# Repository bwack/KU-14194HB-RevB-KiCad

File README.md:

# KU-14194HB-RevB-KiCad

The rare KU14194HB C64 Motherboard schematics and layout. Retraced in and imported from SprintLayout.

[Disclaimer](https://github.com/bwack/KU-14194HB-RevB-KiCad/blob/master/DISCLAIMER.md)

# Original bodges

This PCB is a replica. It includes the mistakes that Commodore made.

It is necessary to cut a trace above R37 on the bottom side, and add a 1K resistor from R37 and up to a via.
See the images folder to where to cut and add a resistor.

Piggyback a 100nF capacitor over CR1.

Notice how the main crystal oscillator Y1 body is grounded with a wire.

In later designs 250407 Reb B I think, 4 piggybacked diodes were introduced to protect the serial lines when hotplugging the disc drive.
I haven't added these myself, but I see the value of having those. I might add instructions here later on how to add the diodes.

# BOM

Please see the [BOM file](bom.csv).

# Interactive-BOM

[The interactive bom html page](https://htmlpreview.github.io/?https://raw.githubusercontent.com/bwack/KU-14194HB-RevB-KiCad/master/interactive-bom/ibom.html) is useful for assembling the board and finding signal traces by using a web browser. Try it here. For a BOM for ordering parts see the BOM above.

# Questions

* Feel free post questions in the issues section. I will provide more information here later.

# Change log

- 2020-01-23: V1.4 PCB improvements:
  - Expansion Port: Larger round solder pads for the shield. Same error in the original.
  - Expansion Port: Connector moved to center of shield. Some traces moved.
  - Left edge: Extended the PCB by 2.2mm.
  - Left edge: Increased track width of the power rails.
  - CAN shield: added two solder pads.
  - RF modulator: added solder pad.
  - Schematics: Rev 1.4. No change.
- 2019-11-12: V1.3 Fixes: Mostly missing values.
  - C88: "1000uF 25V" -> "470uF 50uF". Commodore said 1000 but used 470.
  - R31: "180" -> "1K". A mistake in the commodore schematics.
  - R52: "?" -> "330"
  - R53: "?" -> "100"
  - C86: "?" -> "82pF",
  - C36: "0.1" -> "20pF",
  - R22: missing trace. R22 = 0 Ohm. Parallel to C87 (NC). R22 doesn't matter.
  - C101: is a Y5U. VIC2's decoupling cap. Has a higher dielectric rating. Doesn't matter.
  - C70: 15pF 5%. This is a PAL only board. In later revisions, 16pF is used for NTSC.
 - 2019-11-10 V1.2 Added missing C14 10uF 25V electrolytic capacitor
- 2019-10-15 V1.1 Layout: Fixed missing keying-slot in user port.
- 2019-10-05 V1.0 First release.

# YouTube

A playlist of all the videos:

[](
https://www.youtube.com/watch?v=iNxOm7G6efA&list=PLtQOf_JULmrTGLZCElGG_T1a01JSDP0CP)

# In the wind

forum64.de: The board has some threads at forum64.de (German). May require login.
* [Bilder SHOWROOM für Repro-Boards... KU-14194HB](https://www.forum64.de/index.php?thread/97205-bilder-showroom-f%C3%BCr-repro-boards-ku-14194hb/&pageNo=1)
* [KU-14194 Bestückungs-Thread](https://www.forum64.de/index.php?thread/96336-ku-14194-best%C3%BCckungs-thread/)
* [KU-14194](https://www.forum64.de/index.php?thread/95454-ku-14194/) (long group buy thread)
* [KU-14194 (Replika) ... wer schafft es als Erste/r? Aktuelle Sachstandsberichte ...](https://www.forum64.de/index.php?thread/95518-ku-14194-replika-wer-schafft-es-als-erste-r-aktuelle-sachstandsberichte/)

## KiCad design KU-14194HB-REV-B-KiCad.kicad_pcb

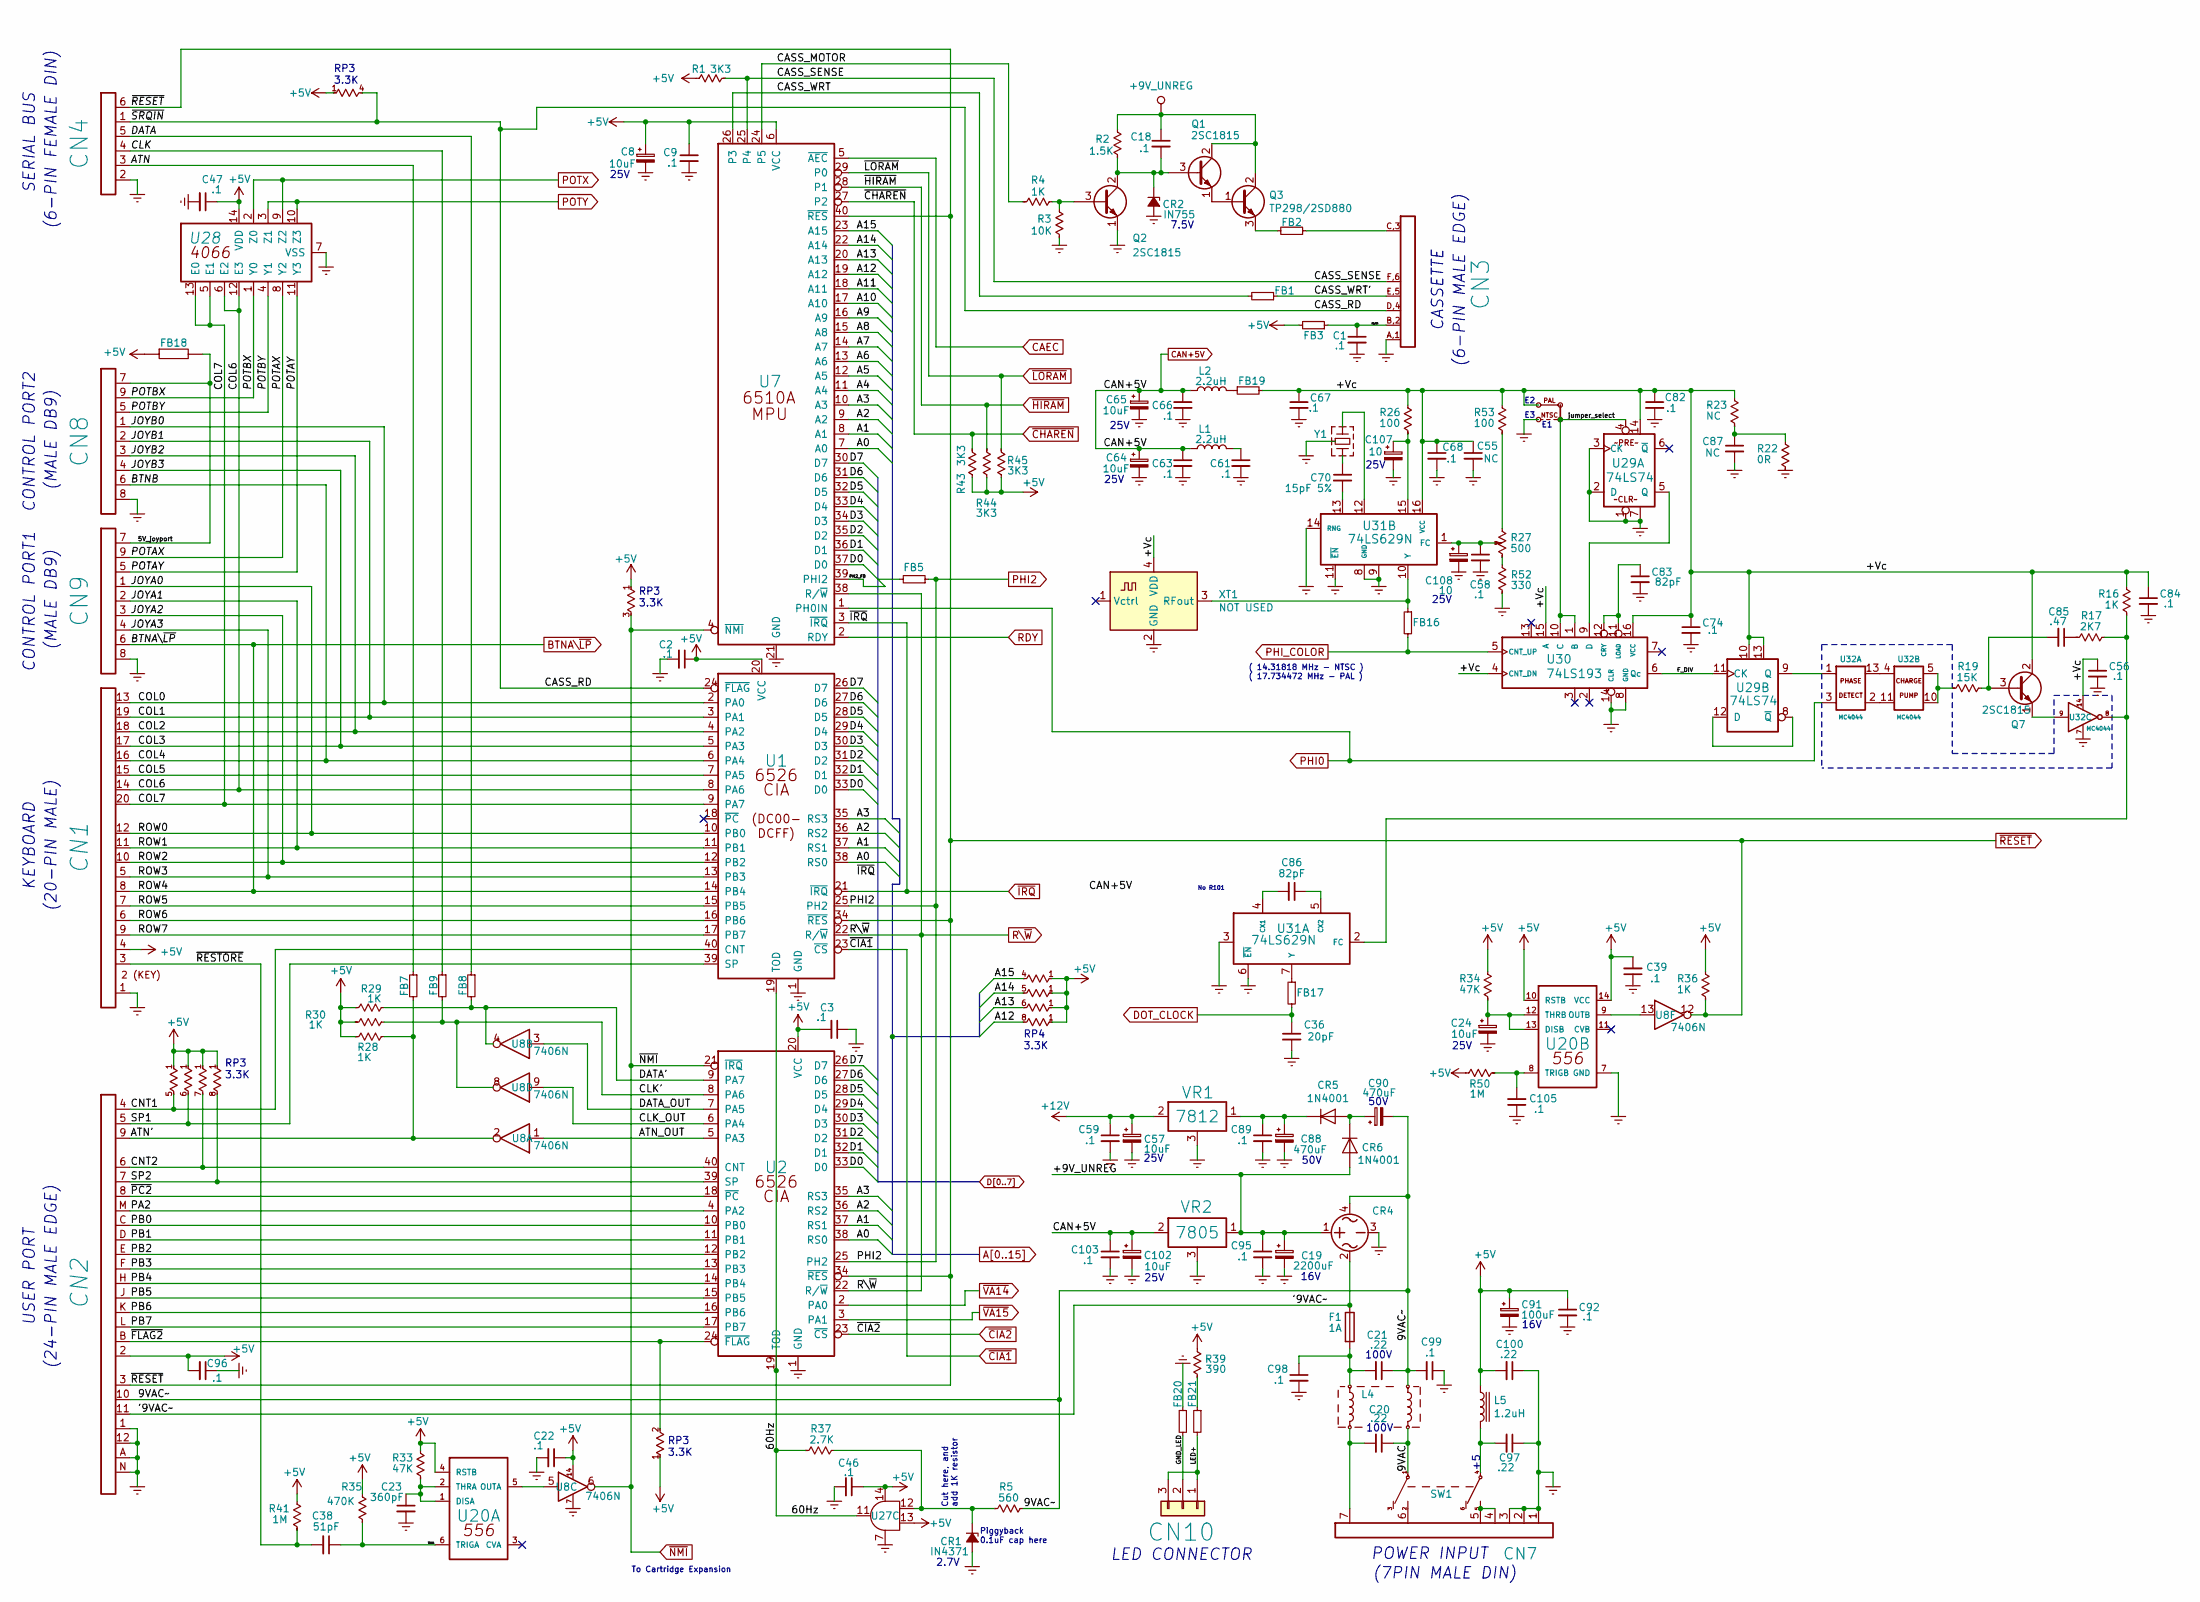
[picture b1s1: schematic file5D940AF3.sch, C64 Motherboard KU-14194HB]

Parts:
C1, C2, C3, C9, C18, C22, C39, C46, C47, C56, C58, C59, C61, C63, C66, C67, C68, C74, C82, C84, C89, C92, C95, C96, C98, C99, C103, C105: .1; CAP_P5.08mm
C8, C24, C57, C64, C65, C102: 10uF; CAP_ELYT_RADIAL_P2.54mm
C19: 2200uF; LARGE_ELECTROLYTIC_33x18_P38.10mm_AXIAL_TH
C20, C21: .22; CAP_POLY_100V_TH_P10.16mm
C23: 360pF; CAP_AXIAL_P12.7mm
C36: 20pF; RESISTOR
C38: 51pF; CAP_AXIAL_P12.7mm
C55, C87: NC; CAP_P5.08mm
C70: 15pF 5%; RESISTOR
C83, C86: 82pF; RESISTOR
C85: .47; CAP_P5.08mm
C88, C90: 470uF; LARGE_ELECTROLYTIC_33x18_P38.10mm_AXIAL_TH
C91: 100uF; CAP_ELYT_RADIAL_P5.08mm
C97, C100: .22; CAP_P5.08mm
C107, C108: 10; CAP_ELYT_RADIAL_P2.54mm
CN1: KEYBOARD_20PIN_MALE; KEYBOARD_CON
CN2: USER_PORT_CON; EDGE_CON_24P
CN3: CASSETTE_PORT_CON; EDGE_CON_12P_TAPE
CN4: SERIAL_BUS_CON; SERIAL_CON_DIN6
CN7: POWER_CON; POWER_CON_DIN7
CN8, CN9: CONTROL_PORT; JOYPORT_DB9
CN10: LED_CONNECTOR; LED_CON
CR1: IN4371; ZENER_12.7mm
CR2: IN755; ZENER_12.7mm
CR4: BRIDGE_RECTIFIER
CR5, CR6: 1N4001; RECTIFIER_TH_P12.7mm
E1: JUMPER_WIRE
F1: 1A; FUSE
FB1, FB2, FB3, FB5, FB7, FB8, FB9, FB16, FB17, FB19, FB20, FB21: FERRITE_NARROW; FERRITE_BEAD_TH_P12.7mm
FB18: FERRITE_BEAD; FERRITE_BEAD_TH_P12.7mm
L1, L2: 2.2uH; RESISTOR
L4: CHOKE
L5: 1.2uH; INDUCTOR_P15.24mm
Q1, Q2, Q7: 2SC1815; Q_NPN_ECB
Q3: TP298/2SD880; TO-220-3_Vertical
R1, R43, R44, R45: 3K3; RESISTOR
R2: 1.5K; RESISTOR
R3: 10K; RESISTOR
R4, R16, R28, R29, R30, R36: 1K; RESISTOR
R5: 560; RESISTOR
R17: 2K7; RESISTOR
R19: 15K; RESISTOR
R22: 0R; RESISTOR
R23: NC; RESISTOR
R26, R53: 100; RESISTOR
R27: 500; POTMETER
R33, R34: 47K; RESISTOR
R35: 470K; RESISTOR
R37: 2.7K; RESISTOR
R39: 390; RESISTOR
R41, R50: 1M; RESISTOR
R52: 330; RESISTOR
RP3: R_ARRAY_7WAY_US; RP_ARRAY_7WAY
RP4: R_ARRAY_9WAY_US; RP_ARRAY_9WAY
SW1: POWER_SWITCH
U1: CIA_U1; DIP40
U2: CIA_U2; DIP40
U7: 6510_MPU; DIP40
U8: 7406N; DIP14
U20: 556; DIP14
U27: 7408_U27; DIP14
U28: 4066_U28; DIP14
U29: 74LS74; DIP14
U30: 74LS193; DIP16
U31: 74LS629N; DIP16
U32: MC4044; DIP14
VR1: 7812; VOTLAGE_REGULATOR_TO220
VR2: 7805; VOTLAGE_REGULATOR_TO220
XT1: NOT USED; DIP4_DIP14_but_4_pins
Y1: Crystal; CRYSTAL

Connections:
+5V: C2.1, C3.2, C8.1, C9.1, C22.1, C39.2, C46.1, C47.1, C91.1, C92.1, C96.2, C100.2, CN1.4, CN2.2, FB3.2, FB18.1, L5.1, R1.1, R28.2, R29.2, R30.2, R33.1, R34.1, R35.1, R36.1, R39.1, R41.1, R43.1, R44.1, R45.1, R50.1, RP3.1, RP4.1, U1.20 (VCC), U2.20 (VCC), U7.6 (VCC), U8.14, U20.4 (RSTB), U20.10 (RSTB), U20.14 (VCC), U27.13, U27.14, U28.14 (VDD); also elsewhere on the board
+9V_UNREG: C18.1, C19.1, C95.1, CR4.1, CR6.2 (A), Q1.2 (C), Q3.2 (C), R2.1, VR2.1; also elsewhere on the board
+12V: C57.1, C59.1, VR1.2; also elsewhere on the board
/Sheet1/5V_FB3: C1.1, CN3.B,2, FB3.1
/Sheet1/5V_joyport: CN8.7, CN9.7, FB18.2
/Sheet1/9VAC: C20.1, L4.3, SW1.1
/Sheet1/9VAC~~: C21.1, C90.2, C99.2, CN2.10, CR4.4, L4.4, R5.1
/Sheet1/60Hz: R37.2, U1.19 (TOD), U2.19 (TOD), U27.11
/Sheet1/'9VAC~~: CN2.11, CR4.2, F1.1
/Sheet1/+Vc: C55.1, C56.1, C67.1, C68.1, C74.1, C82.1, C84.1, E1.1, FB19.2, Q7.2 (C), R16.1, R23.1, R26.1, R53.1, U29.10, U29.13, U29.14, U30.4 (CNT_DN), U30.15 (A), U30.16 (VCC), U31.16 (VCC), U32.14, XT1.4 (VDD)
/Sheet1/ATN: CN4.3, FB7.1
/Sheet1/ATN': CN2.9, FB7.2, R28.1, U8.2
/Sheet1/ATN_OUT: U2.5 (PA3), U8.1
/Sheet1/BTNB: CN1.16, CN8.6, U1.6 (PA4)
/Sheet1/CASS_MOTOR: R4.2, U7.24 (P5)
/Sheet1/CASS_RD: CN3.D,4, CN4.1, RP3.4, U1.24 (~FLAG~)
/Sheet1/CASS_SENSE: CN3.F,6, R1.2, U7.25 (P4)
/Sheet1/CASS_WRT: FB1.2, U7.26 (P3)
/Sheet1/CASS_WRT': CN3.E,5, FB1.1
/Sheet1/CLK: CN4.4, FB9.1
/Sheet1/CLK': FB9.2, R30.1, U2.8 (PA6), U8.8
/Sheet1/CLK_OUT: U2.6 (PA4), U8.9
/Sheet1/CNT1: CN2.4, RP3.5, U1.40 (CNT)
/Sheet1/CNT2: CN2.6, RP3.7, U2.40 (CNT)
/Sheet1/COL0: CN1.13, CN8.1, U1.2 (PA0)
/Sheet1/COL1: CN1.19, CN8.2, U1.3 (PA1)
/Sheet1/COL2: CN1.18, CN8.3, U1.4 (PA2)
/Sheet1/COL3: CN1.17, CN8.4, U1.5 (PA3)
/Sheet1/COL5: CN1.15, U1.7 (PA5)
/Sheet1/COL6: CN1.14, U1.8 (PA6), U28.6 (E2), U28.12 (E3)
/Sheet1/COL7: CN1.20, U1.9 (PA7), U28.5 (E1), U28.13 (E0)
/Sheet1/DATA: CN4.5, FB8.1
/Sheet1/DATA': FB8.2, R29.1, U2.9 (PA7), U8.4
/Sheet1/DATA_OUT: U2.7 (PA5), U8.3
/Sheet1/F_DIV: U29.11 (CK), U30.6 (Qc)
/Sheet1/GND_LED: CN10.2, FB20.2
/Sheet1/JOYA0: CN1.12, CN9.1, U1.10 (PB0)
/Sheet1/JOYA1: CN1.11, CN9.2, U1.11 (PB1)
/Sheet1/JOYA2: CN1.10, CN9.3, U1.12 (PB2)
/Sheet1/JOYA3: CN1.5, CN9.4, U1.13 (PB3)
/Sheet1/LED+: CN10.1, CN10.3, FB21.2
/Sheet1/PA2: CN2.M, U2.4 (PA2)
/Sheet1/PB0: CN2.C, U2.10 (PB0)
/Sheet1/PB1: CN2.D, U2.11 (PB1)
/Sheet1/PB2: CN2.E, U2.12 (PB2)
/Sheet1/PB3: CN2.F, U2.13 (PB3)
/Sheet1/PB4: CN2.H, U2.14 (PB4)
/Sheet1/PB5: CN2.J, U2.15 (PB5)
/Sheet1/PB6: CN2.K, U2.16 (PB6)
/Sheet1/PB7: CN2.L, U2.17 (PB7)
/Sheet1/PH2_FB: FB5.2, U7.39 (PHI2)
/Sheet1/POTAX: CN9.9, U28.8 (Y2)
/Sheet1/POTAY: CN9.5, U28.11 (Y3)
/Sheet1/POTBX: CN8.9, U28.1 (Y0)
/Sheet1/POTBY: CN8.5, U28.4 (Y1)
/Sheet1/ROW5: CN1.7, U1.15 (PB5)
/Sheet1/ROW6: CN1.6, U1.16 (PB6)
/Sheet1/ROW7: CN1.9, U1.17 (PB7)
/Sheet1/SP1: CN2.5, RP3.6, U1.39 (SP)
/Sheet1/SP2: CN2.7, RP3.8, U2.39 (SP)
/Sheet1/TRIGA: C38.1, R35.2, U20.6 (TRIGA)
/Sheet1/jumper_select: E1.C, U29.4, U30.1 (B), U30.10 (C)
/Sheet1/~FLAG2~: CN2.B, RP3.2, U2.24 (~FLAG~)
/Sheet1/~PC2~: CN2.8, U2.18 (~PC~)
/Sheet1/~RESTORE~: C38.2, CN1.3, R41.2
A0: U1.38 (RS0), U2.38 (RS0), U7.7 (A0); also elsewhere on the board
A1: U1.37 (RS1), U2.37 (RS1), U7.8 (A1); also elsewhere on the board
A2: U1.36 (RS2), U2.36 (RS2), U7.9 (A2); also elsewhere on the board
A3: U1.35 (RS3), U2.35 (RS3), U7.10 (A3); also elsewhere on the board
A4: U7.11 (A4); also elsewhere on the board
A5: U7.12 (A5); also elsewhere on the board
A6: U7.13 (A6); also elsewhere on the board
A7: U7.14 (A7); also elsewhere on the board
A8: U7.15 (A8); also elsewhere on the board
A9: U7.16 (A9); also elsewhere on the board
A10: U7.17 (A10); also elsewhere on the board
A11: U7.18 (A11); also elsewhere on the board
A12: RP4.8, U7.19 (A12); also elsewhere on the board
A13: RP4.6, U7.20 (A13); also elsewhere on the board
A14: RP4.5, U7.22 (A14); also elsewhere on the board
A15: RP4.4, U7.23 (A15); also elsewhere on the board
BTNA\~LP~: CN1.8, CN9.6, U1.14 (PB4); also elsewhere on the board
CAEC: U7.5 (~AEC~); also elsewhere on the board
CAN+5V: C63.1, C64.1, C65.1, C66.1, C102.1, C103.1, L1.1, L2.1, VR2.2; also elsewhere on the board
D0: U1.33 (D0), U2.33 (D0), U7.37 (D0); also elsewhere on the board
D1: U1.32 (D1), U2.32 (D1), U7.36 (D1); also elsewhere on the board
D2: U1.31 (D2), U2.31 (D2), U7.35 (D2); also elsewhere on the board
D3: U1.30 (D3), U2.30 (D3), U7.34 (D3); also elsewhere on the board
D4: U1.29 (D4), U2.29 (D4), U7.33 (D4); also elsewhere on the board
D5: U1.28 (D5), U2.28 (D5), U7.32 (D5); also elsewhere on the board
D6: U1.27 (D6), U2.27 (D6), U7.31 (D6); also elsewhere on the board
D7: U1.26 (D7), U2.26 (D7), U7.30 (D7); also elsewhere on the board
DOT_CLOCK: C36.1, FB17.2; also elsewhere on the board
unnamed: C18.2, CR2.1 (K), Q1.3 (B), Q2.2 (C), R2.2
unnamed: C20.2, CN7.7, L4.2
unnamed: C21.2, C98.1, F1.2, L4.1
unnamed: C23.1, R33.2, U20.1 (DISA), U20.2 (THRA)
unnamed: C24.1, R34.2, U20.12 (THRB), U20.13 (DISB)
unnamed: C61.1, L1.2
unnamed: C70.1, Y1.2
unnamed: C70.2, U31.13
unnamed: C83.1, U30.11 (LOAD), U30.12 (CRY)
unnamed: C85.1, R17.2
unnamed: C85.2, Q7.3 (B), R19.1
unnamed: C86.1, U31.5 (CX2)
unnamed: C86.2, U31.4 (CX1)
unnamed: C87.1, R22.1, R23.2
unnamed: C88.1, C89.1, CR5.1 (K), VR1.1
unnamed: C90.1, CR5.2 (A), CR6.1 (K)
unnamed: C97.2, L5.2, SW1.4
unnamed: C105.2, R50.2, U20.8 (TRIGB)
unnamed: C107.1, R26.2, U31.15
unnamed: C58.1, C108.1, R27.3, U31.1 (FC)
unnamed: CN3.C,3, FB2.1
unnamed: CN7.4, CN7.5, SW1.5
unnamed: CN7.6, SW1.2
unnamed: CR1.1 (K), R5.2, R37.1, U27.12
unnamed: FB2.2, Q3.3 (E)
unnamed: FB16.1, U31.10 (Y), XT1.3 (RFout)
unnamed: FB17.1, U31.7 (Y)
unnamed: FB19.1, L2.2
unnamed: FB21.1, R39.2
unnamed: Q1.1 (E), Q3.1 (B)
unnamed: Q2.3 (B), R3.1, R4.1
unnamed: Q7.1 (E), U32.9
unnamed: R16.2, R17.1, U31.2 (FC), U32.8
unnamed: R19.2, U32.5, U32.10
unnamed: R27.1, R53.2
unnamed: R27.2, R52.1
unnamed: U8.5, U20.5 (OUTA)
unnamed: U8.13, U20.9 (OUTB)
unnamed: U29.5 (Q), U30.9 (D)
unnamed: U29.9 (Q), U32.1
unnamed: U29.8 (~Q~), U29.12 (D)
unnamed: U31.12, Y1.1
unnamed: U32.2, U32.11
unnamed: U32.4, U32.13
PHI0: U7.1 (PH0IN), U32.3; also elsewhere on the board
PHI2: FB5.1, U1.25 (PH2), U2.25 (PH2); also elsewhere on the board
PHI_COLOR: FB16.2, U30.5 (CNT_UP); also elsewhere on the board
POTX: U28.2 (Z0), U28.9 (Z2); also elsewhere on the board
POTY: U28.3 (Z1), U28.10 (Z3); also elsewhere on the board
RDY: U7.2 (RDY); also elsewhere on the board
R\~W~: U1.22 (R/~W~), U2.22 (R/~W~), U7.38 (R/~W~); also elsewhere on the board
~CHAREN~: R43.2, U7.27 (P2); also elsewhere on the board
~CIA1~: U1.23 (~CS~); also elsewhere on the board
~CIA2~: U2.23 (~CS~); also elsewhere on the board
~HIRAM~: R44.2, U7.28 (P1); also elsewhere on the board
~IRQ~: U1.21 (~IRQ~), U7.3 (~IRQ~); also elsewhere on the board
~LORAM~: R45.2, U7.29 (P0); also elsewhere on the board
~NMI~: RP3.3, U2.21 (~IRQ~), U7.4 (~NMI~), U8.6; also elsewhere on the board
~RESET~: CN2.3, CN4.6, R36.2, U1.34 (~RES~), U2.34 (~RES~), U7.40 (~RES~), U8.12; also elsewhere on the board
~VA14~: U2.2 (PA0); also elsewhere on the board
~VA15~: U2.3 (PA1); also elsewhere on the board

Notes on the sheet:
SERIAL BUS
(6-PIN FEMALE DIN)
(24-PIN MALE EDGE)
USER PORT
RP3 3.3K
KEYBOARD
(20-PIN MALE)
(MALE DB9)
CONTROL PORT2
CONTROL PORT1
25V
2.7V
Cut here, and add 1K resistor
Piggyback 0.1uF cap here
RP4 3.3K
7.5V
(6-PIN MALE EDGE)
CASSETTE
LED CONNECTOR
100V
POWER INPUT
(7PIN MALE DIN)
16V
50V
No R101
( 14.31818 MHz - NTSC ) ( 17.734472 MHz - PAL )
To Cartridge Expansion

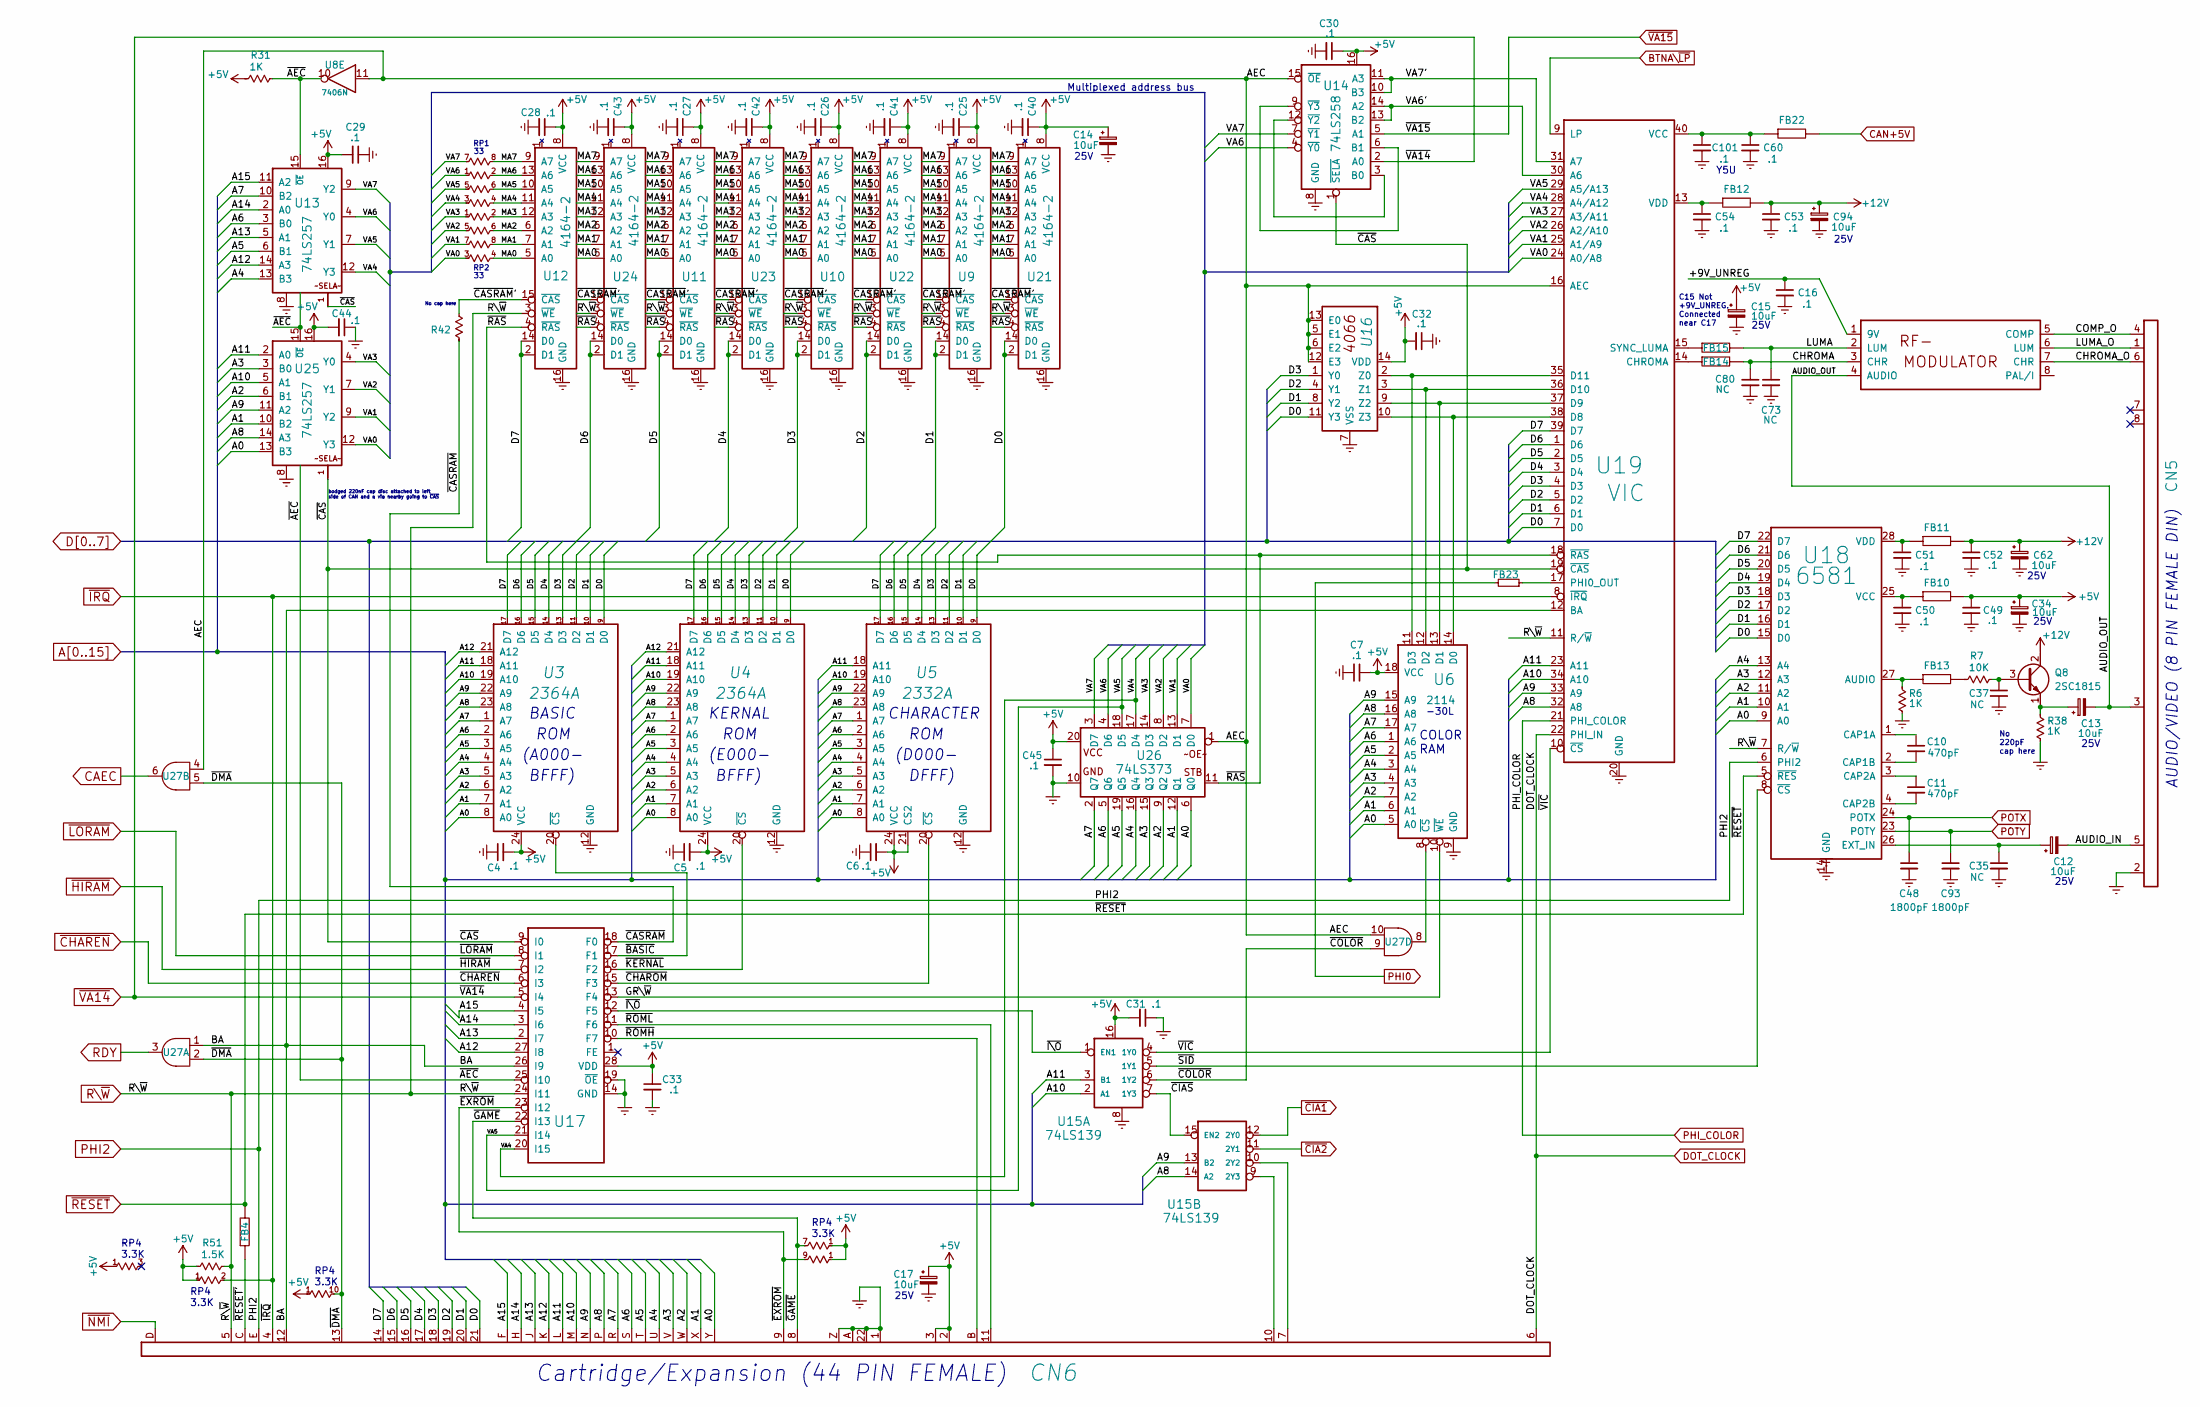
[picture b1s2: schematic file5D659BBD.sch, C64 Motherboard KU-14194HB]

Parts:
C4, C5, C6, C7, C16, C25, C26, C27, C28, C29, C30, C31, C32, C33, C40, C41, C42, C43, C44, C45, C50, C51, C53, C54, C60, C101: .1; CAP_P5.08mm
C10, C11: 470pF; CAP_AXIAL_P10.16mm
C12, C13, C14, C15, C17, C34, C62, C94: 10uF; CAP_ELYT_RADIAL_P2.54mm
C35, C37: NC; CAP_P5.08mm
C48, C93: 1800pF; RESISTOR_10.16mm
C49, C52: .1; CAP_P12mm
C73, C80: NC; CAP_AXIAL_P12.7mm
CN5: AV_CONN; AV_CON_DIN8
CN6: EXPANSION_PORT
FB4, FB10, FB11, FB12, FB13, FB14, FB15, FB22: FERRITE_BEAD; FERRITE_BEAD_TH_P12.7mm
FB23: FERRITE_NARROW; FERRITE_BEAD_TH_P12.7mm
M1: MODULATOR_LONGBOARD; MODULATOR_PORT_LONGBOARD
Q8: 2SC1815; Q_NPN_ECB
R6, R31, R38: 1K; RESISTOR
R7: 10K; RESISTOR
R42: RESISTOR
R51: 1.5K; RESISTOR
RP1, RP2: 33; RP_ARRAY_7WAY
RP4: R_ARRAY_9WAY_US; RP_ARRAY_9WAY
U3, U4: 2364A; DIP24
U5: 2332A; DIP24
U6: 2114; DIP18
U8: 7406N; DIP14
U9, U10, U11, U12, U21, U22, U23, U24: 4164-2; DIP16
U13, U25: 74LS257; DIP16
U14: 74LS258; DIP16
U15: 74LS139; DIP16
U16: 4066_U28; DIP14
U17: PLA_U17; DIP28
U18: 6581; DIP28
U19: VIC; DIP40
U26: 74LS373; DIP20
U27: 7408_U27; DIP14

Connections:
+5V: C4.2, C5.2, C6.2, C7.1, C14.1, C15.1, C17.1, C25.1, C26.1, C27.1, C28.1, C29.2, C30.1, C31.2, C32.2, C33.1, C34.1, C40.1, C41.1, C42.1, C43.1, C44.2, C45.1, C49.1, CN6.2, CN6.3, FB10.2, R31.2, R51.2, RP4.1, U3.24 (VCC), U4.24 (VCC), U5.21 (CS2), U5.24 (VCC), U6.18 (VCC), U9.8 (VCC), U10.8 (VCC), U11.8 (VCC), U12.8 (VCC), U13.16, U14.16, U15.16, U16.14 (VDD), U17.28 (VDD), U21.8 (VCC), U22.8 (VCC), U23.8 (VCC), U24.8 (VCC), U25.16, U26.20; also elsewhere on the board
+9V_UNREG: C16.1, M1.1 (9V); also elsewhere on the board
+12V: C52.1, C53.1, C62.1, C94.1, FB11.2, FB12.2, Q8.2 (C); also elsewhere on the board
/Sheet5D659BBD/AEC: U8.11, U14.15 (~OE~), U16.5 (E1), U16.6 (E2), U16.12 (E3), U16.13 (E0), U19.16 (AEC), U26.1, U27.4, U27.10
/Sheet5D659BBD/AUDIO_IN: C12.2, CN5.5
/Sheet5D659BBD/AUDIO_OUT: C13.2, CN5.3, M1.4 (AUDIO)
/Sheet5D659BBD/BA: CN6.12, U17.26 (I9), U19.12 (BA), U27.1
/Sheet5D659BBD/CHROMA: C80.1, FB14.2, M1.3 (CHR)
/Sheet5D659BBD/CHROMA_O: CN5.6, M1.7 (CHR)
/Sheet5D659BBD/COMP_O: CN5.4, M1.5 (COMP)
/Sheet5D659BBD/GR\~W~: U6.10 (~WE~), U17.13 (F4)
/Sheet5D659BBD/LUMA: C73.1, FB15.2, M1.2 (LUM)
/Sheet5D659BBD/LUMA_O: CN5.1, M1.6 (LUM)
/Sheet5D659BBD/MA0: RP2.4, U9.5 (A0), U10.5 (A0), U11.5 (A0), U12.5 (A0), U21.5 (A0), U22.5 (A0), U23.5 (A0), U24.5 (A0)
/Sheet5D659BBD/MA1: RP2.8, U9.7 (A1), U10.7 (A1), U11.7 (A1), U12.7 (A1), U21.7 (A1), U22.7 (A1), U23.7 (A1), U24.7 (A1)
/Sheet5D659BBD/MA2: RP2.6, U9.6 (A2), U10.6 (A2), U11.6 (A2), U12.6 (A2), U21.6 (A2), U22.6 (A2), U23.6 (A2), U24.6 (A2)
/Sheet5D659BBD/MA3: RP2.2, U9.12 (A3), U10.12 (A3), U11.12 (A3), U12.12 (A3), U21.12 (A3), U22.12 (A3), U23.12 (A3), U24.12 (A3)
/Sheet5D659BBD/MA4: RP1.4, U9.11 (A4), U10.11 (A4), U11.11 (A4), U12.11 (A4), U21.11 (A4), U22.11 (A4), U23.11 (A4), U24.11 (A4)
/Sheet5D659BBD/MA5: RP1.6, U9.10 (A5), U10.10 (A5), U11.10 (A5), U12.10 (A5), U21.10 (A5), U22.10 (A5), U23.10 (A5), U24.10 (A5)
/Sheet5D659BBD/MA6: RP1.2, U9.13 (A6), U10.13 (A6), U11.13 (A6), U12.13 (A6), U21.13 (A6), U22.13 (A6), U23.13 (A6), U24.13 (A6)
/Sheet5D659BBD/MA7: RP1.8, U9.9 (A7), U10.9 (A7), U11.9 (A7), U12.9 (A7), U21.9 (A7), U22.9 (A7), U23.9 (A7), U24.9 (A7)
/Sheet5D659BBD/VA0: RP2.3, U19.24 (A0/A8), U25.12 (Y3), U26.7 (D0)
/Sheet5D659BBD/VA1: RP2.7, U19.25 (A1/A9), U25.9 (Y2), U26.13 (D1)
/Sheet5D659BBD/VA2: RP2.5, U19.26 (A2/A10), U25.7 (Y1), U26.8 (D2)
/Sheet5D659BBD/VA3: RP2.1, U19.27 (A3/A11), U25.4 (Y0), U26.14 (D3)
/Sheet5D659BBD/VA4: RP1.3, U13.12 (Y3), U17.20 (I15), U19.28 (A4/A12), U26.17 (D4)
/Sheet5D659BBD/VA5: RP1.5, U13.7 (Y1), U17.21 (I14), U19.29 (A5/A13), U26.18 (D5)
/Sheet5D659BBD/VA6: RP1.1, U13.4 (Y0), U14.4 (~Y0~), U26.4 (D6)
/Sheet5D659BBD/VA6': U14.13 (B2), U14.14 (A2), U19.30 (A6)
/Sheet5D659BBD/VA7: RP1.7, U13.9 (Y2), U14.7 (~Y1~), U26.3 (D7)
/Sheet5D659BBD/VA7': U14.10 (B3), U14.11 (A3), U19.31 (A7)
/Sheet5D659BBD/~AEC~: R31.1, U8.10, U13.15 (~OE~), U17.25 (I10), U25.15 (~OE~)
/Sheet5D659BBD/~BASIC~: U3.20 (~CS~), U17.17 (F1)
/Sheet5D659BBD/~CASRAM~: R42.2, U17.18 (F0)
/Sheet5D659BBD/~CASRAM~': R42.1, U9.15 (~CAS~), U10.15 (~CAS~), U11.15 (~CAS~), U12.15 (~CAS~), U21.15 (~CAS~), U22.15 (~CAS~), U23.15 (~CAS~), U24.15 (~CAS~)
/Sheet5D659BBD/~CAS~: U13.1 (~SELA~), U14.1 (~SELA~), U17.9 (I0), U19.19 (~CAS~), U25.1 (~SELA~)
/Sheet5D659BBD/~CHAROM~: U5.20 (~CS~), U17.15 (F3)
/Sheet5D659BBD/~CIAS~: U15.7 (1Y3), U15.15 (EN2)
/Sheet5D659BBD/~COLOR~: U15.6 (1Y2), U27.9
/Sheet5D659BBD/~DMA~: CN6.13, RP4.10, U27.2, U27.5
/Sheet5D659BBD/~EXROM~: CN6.9, RP4.9, U17.23 (I12)
/Sheet5D659BBD/~GAME~: CN6.8, RP4.7, U17.22 (I13)
/Sheet5D659BBD/~I\O~: U15.1 (EN1), U17.12 (F5)
/Sheet5D659BBD/~KERNAL: U4.20 (~CS~), U17.16 (F2)
/Sheet5D659BBD/~RAS~: U9.4 (~RAS~), U10.4 (~RAS~), U11.4 (~RAS~), U12.4 (~RAS~), U19.18 (~RAS~), U21.4 (~RAS~), U22.4 (~RAS~), U23.4 (~RAS~), U24.4 (~RAS~), U26.11
/Sheet5D659BBD/~RESET'~: CN6.C, FB4.1
/Sheet5D659BBD/~ROMH~: CN6.B, U17.10 (F7)
/Sheet5D659BBD/~ROML~: CN6.11, U17.11 (F6)
/Sheet5D659BBD/~SID~: U15.5 (1Y1), U18.8 (~CS~)
/Sheet5D659BBD/~VIC~: U15.4 (1Y0), U19.10 (~CS~)
A0: CN6.Y, U3.8 (A0), U4.8 (A0), U5.8 (A0), U6.5 (A0), U18.9 (A0), U25.13 (B3), U26.6 (Q0); also elsewhere on the board
A1: CN6.X, U3.7 (A1), U4.7 (A1), U5.7 (A1), U6.6 (A1), U18.10 (A1), U25.10 (B2), U26.12 (Q1); also elsewhere on the board
A2: CN6.W, U3.6 (A2), U4.6 (A2), U5.6 (A2), U6.7 (A2), U18.11 (A2), U25.6 (B1), U26.9 (Q2); also elsewhere on the board
A3: CN6.V, U3.5 (A3), U4.5 (A3), U5.5 (A3), U6.4 (A3), U18.12 (A3), U25.3 (B0), U26.15 (Q3); also elsewhere on the board
A4: CN6.U, U3.4 (A4), U4.4 (A4), U5.4 (A4), U6.3 (A4), U13.13 (B3), U18.13 (A4), U26.16 (Q4); also elsewhere on the board
A5: CN6.T, U3.3 (A5), U4.3 (A5), U5.3 (A5), U6.2 (A5), U13.6 (B1), U26.19 (Q5); also elsewhere on the board
A6: CN6.S, U3.2 (A6), U4.2 (A6), U5.2 (A6), U6.1 (A6), U13.3 (B0), U26.5 (Q6); also elsewhere on the board
A7: CN6.R, U3.1 (A7), U4.1 (A7), U5.1 (A7), U6.17 (A7), U13.10 (B2), U26.2 (Q7); also elsewhere on the board
A8: CN6.P, U3.23 (A8), U4.23 (A8), U5.23 (A8), U6.16 (A8), U15.14 (A2), U19.32 (A8), U25.14 (A3); also elsewhere on the board
A9: CN6.N, U3.22 (A9), U4.22 (A9), U5.22 (A9), U6.15 (A9), U15.13 (B2), U19.33 (A9), U25.11 (A2); also elsewhere on the board
A10: CN6.M, U3.19 (A10), U4.19 (A10), U5.19 (A10), U15.2 (A1), U19.34 (A10), U25.5 (A1); also elsewhere on the board
A11: CN6.L, U3.18 (A11), U4.18 (A11), U5.18 (A11), U15.3 (B1), U19.23 (A11), U25.2 (A0); also elsewhere on the board
A12: CN6.K, U3.21 (A12), U4.21 (A12), U13.14 (A3), U17.27 (I8); also elsewhere on the board
A13: CN6.J, U13.5 (A1), U17.2 (I7); also elsewhere on the board
A14: CN6.H, U13.2 (A0), U17.3 (I6); also elsewhere on the board
A15: CN6.F, U13.11 (A2), U17.4 (I5); also elsewhere on the board
BTNA\~LP~: U19.9 (LP); also elsewhere on the board
CAEC: U27.6; also elsewhere on the board
CAN+5V: FB22.2; also elsewhere on the board
D0: CN6.21, U3.9 (D0), U4.9 (D0), U5.9 (D0), U16.11 (Y3), U18.15 (D0), U19.7 (D0), U21.2 (D1), U21.14 (D0); also elsewhere on the board
D1: CN6.20, U3.10 (D1), U4.10 (D1), U5.10 (D1), U9.2 (D1), U9.14 (D0), U16.8 (Y2), U18.16 (D1), U19.6 (D1); also elsewhere on the board
D2: CN6.19, U3.11 (D2), U4.11 (D2), U5.11 (D2), U16.4 (Y1), U18.17 (D2), U19.5 (D2), U22.2 (D1), U22.14 (D0); also elsewhere on the board
D3: CN6.18, U3.13 (D3), U4.13 (D3), U5.13 (D3), U10.2 (D1), U10.14 (D0), U16.1 (Y0), U18.18 (D3), U19.4 (D3); also elsewhere on the board
D4: CN6.17, U3.14 (D4), U4.14 (D4), U5.14 (D4), U18.19 (D4), U19.3 (D4), U23.2 (D1), U23.14 (D0); also elsewhere on the board
D5: CN6.16, U3.15 (D5), U4.15 (D5), U5.15 (D5), U11.2 (D1), U11.14 (D0), U18.20 (D5), U19.2 (D5); also elsewhere on the board
D6: CN6.15, U3.16 (D6), U4.16 (D6), U5.16 (D6), U18.21 (D6), U19.1 (D6), U24.2 (D1), U24.14 (D0); also elsewhere on the board
D7: CN6.14, U3.17 (D7), U4.17 (D7), U5.17 (D7), U12.2 (D1), U12.14 (D0), U18.22 (D7), U19.39 (D7); also elsewhere on the board
DOT_CLOCK: CN6.6, U19.22 (PHI_IN); also elsewhere on the board
unnamed: C10.1, U18.1 (CAP1A)
unnamed: C10.2, U18.2 (CAP1B)
unnamed: C11.1, U18.3 (CAP2A)
unnamed: C11.2, U18.4 (CAP2B)
unnamed: C12.1, C35.1, U18.26 (EXT_IN)
unnamed: C13.1, Q8.1 (E), R38.2
unnamed: C37.1, Q8.3 (B), R7.1
unnamed: C50.1, FB10.1, U18.25 (VCC)
unnamed: C51.1, FB11.1, U18.28 (VDD)
unnamed: C54.1, FB12.1, U19.13 (VDD)
unnamed: C60.1, C101.1, FB22.1, U19.40 (VCC)
unnamed: CN6.7, U15.10 (2Y2)
unnamed: CN6.10, U15.9 (2Y3)
unnamed: FB13.1, R6.2, U18.27 (AUDIO)
unnamed: FB13.2, R7.2
unnamed: FB14.1, U19.14 (CHROMA)
unnamed: FB15.1, U19.15 (SYNC_LUMA)
unnamed: FB23.1, U19.17 (PHI0_OUT)
unnamed: U14.6 (B1), U14.9 (~Y3~)
unnamed: U14.3 (B0), U14.12 (~Y2~)
unnamed: U6.11 (D3), U16.2 (Z0), U19.35 (D11)
unnamed: U6.12 (D2), U16.3 (Z1), U19.36 (D10)
unnamed: U6.13 (D1), U16.9 (Z2), U19.37 (D9)
unnamed: U6.14 (D0), U16.10 (Z3), U19.38 (D8)
unnamed: U6.8 (~CS~), U27.8
PHI0: FB23.2; also elsewhere on the board
PHI2: CN6.E, U18.6 (PHI2); also elsewhere on the board
PHI_COLOR: U19.21 (PHI_COLOR); also elsewhere on the board
POTX: C48.1, U18.24 (POTX); also elsewhere on the board
POTY: C93.1, U18.23 (POTY); also elsewhere on the board
RDY: U27.3; also elsewhere on the board
R\~W~: CN6.5, R51.1, U9.3 (~WE~), U10.3 (~WE~), U11.3 (~WE~), U12.3 (~WE~), U17.24 (I11), U18.7 (R/~W~), U19.11 (R/~W~), U21.3 (~WE~), U22.3 (~WE~), U23.3 (~WE~), U24.3 (~WE~); also elsewhere on the board
~CHAREN~: U17.6 (I3); also elsewhere on the board
~CIA1~: U15.12 (2Y0); also elsewhere on the board
~CIA2~: U15.11 (2Y1); also elsewhere on the board
~HIRAM~: U17.7 (I2); also elsewhere on the board
~IRQ~: CN6.4, RP4.2, U19.8 (~IRQ~); also elsewhere on the board
~LORAM~: U17.8 (I1); also elsewhere on the board
~NMI~: CN6.D; also elsewhere on the board
~RESET~: FB4.2, U18.5 (~RES~); also elsewhere on the board
~VA14~: U14.2 (A0), U17.5 (I4); also elsewhere on the board
~VA15~: U14.5 (A1); also elsewhere on the board

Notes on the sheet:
RP1
RP2
bodged 220nF cap disc attached to left side of CAN and a via nearby going to ~CAS~
No cap here
BASIC
ROM
(A000-
BFFF)
KERNAL
(E000-
CHARACTER
(D000-
DFFF)
RP4 3.3K
Cartridge/Expansion (44 PIN FEMALE)
Multiplexed address bus
25V
-30L
COLOR RAM
AUDIO/VIDEO (8 PIN FEMALE DIN)
No 220pF cap here
C15 Not +9V_UNREG. Connected near C17
Y5U

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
